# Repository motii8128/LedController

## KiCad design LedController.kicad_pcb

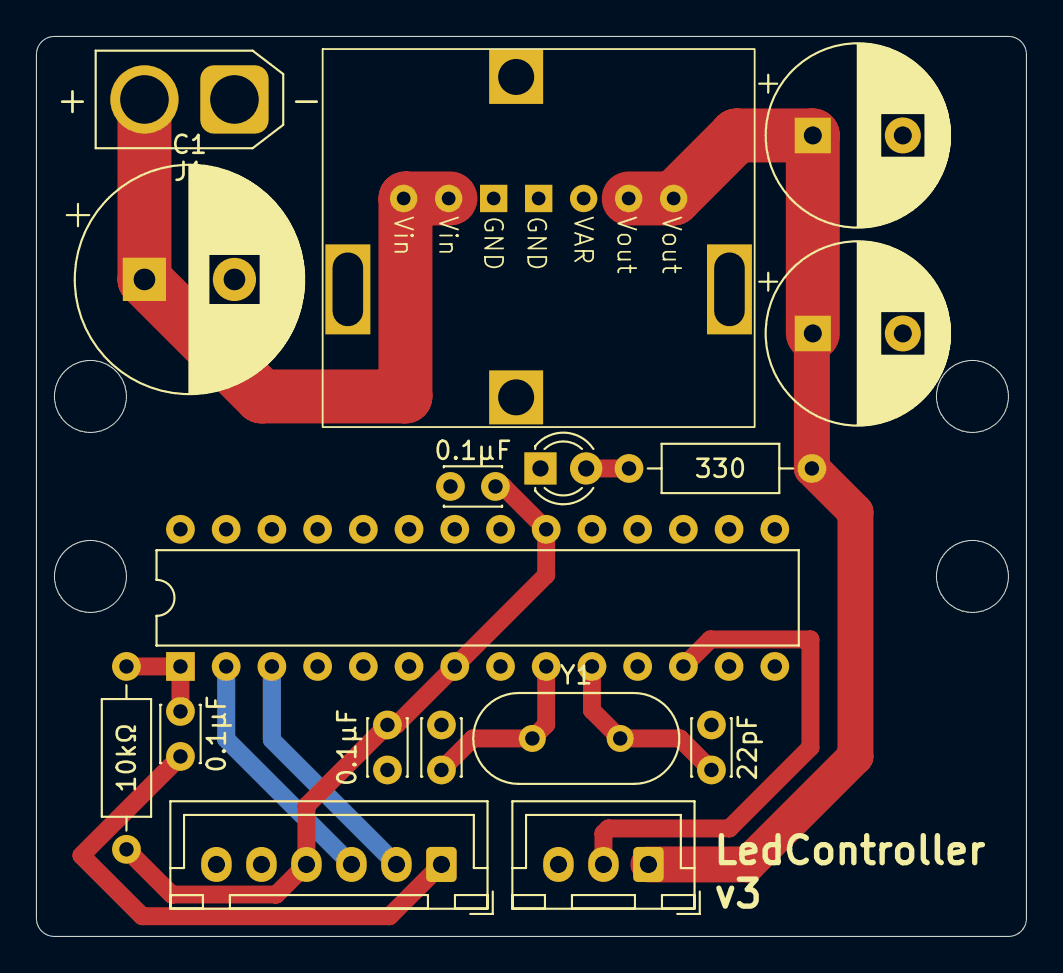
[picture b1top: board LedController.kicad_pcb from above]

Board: 2 copper layers, 55.0 x 50.0 mm, 17 parts (0 on the bottom side), 12 nets.

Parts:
0.1μF, 0.1μF#2, 0.1μF#3: 0.1uF; C_Disc_D3.0mm_W2.0mm_P2.50mm
10kΩ, 330: 10kΩ; R_Axial_DIN0207_L6.3mm_D2.5mm_P10.16mm_Horizontal
22pF: 22pF; C_Disc_D3.0mm_W2.0mm_P2.50mm
1000μF10V: 1000uF10V; CP_Radial_D10.0mm_P5.00mm
C1: 1000uF50V; CP_Radial_D12.5mm_P5.00mm
C2: 1000uF10V; CP_Radial_D10.0mm_P5.00mm
C4: 22pF; C_Disc_D3.0mm_W2.0mm_P2.50mm
D1: LED; LED_D3.0mm
J1: Batt; AMASS_XT30U-M_1x02_P5.0mm_Vertical
J3: Output; JST_XH_B3B-XH-A_1x03_P2.50mm_Vertical
RST: USB; JST_XH_B6B-XH-A_1x06_P2.50mm_Vertical
U1: MPD7K020S
U2: ATmega328P-P; DIP-28_W7.62mm
Y1: 16MHz; Crystal_HC49-4H_Vertical

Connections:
+5V: 330.2, 1000μF10V.1, C2.1, J3.1, U1.6 (Vout), U1.7 (Vout)
GND: 0.1μF.2, 0.1μF#3.1, 22pF.2, 1000μF10V.2, C1.2, C2.2, C4.2, D1.1 (K), J1.1, J3.3, RST.6, U1.3 (GND), U1.4 (GND), U2.8 (GND), U2.22 (GND)
unnamed: 330.1, D1.2 (A)
unnamed: C1.1, J1.2, U1.1 (Vin), U1.2 (Vin)
unnamed: 0.1μF#2.1, RST.1
unnamed: J3.2, U2.12 (PD6)
unnamed: C4.1, U2.9 (XTAL1/PB6), Y1.1
unnamed: 22pF.1, U2.10 (XTAL2/PB7), Y1.2
unnamed: 0.1μF#2.2, 10kΩ.2, U2.1 (~RESET/PC6)
RXD: RST.2, U2.3 (PD1)
TXD: RST.3, U2.2 (PD0)
VCC: 0.1μF.1, 0.1μF#3.2, 10kΩ.1, RST.4, U2.7 (VCC), U2.20 (AVCC)

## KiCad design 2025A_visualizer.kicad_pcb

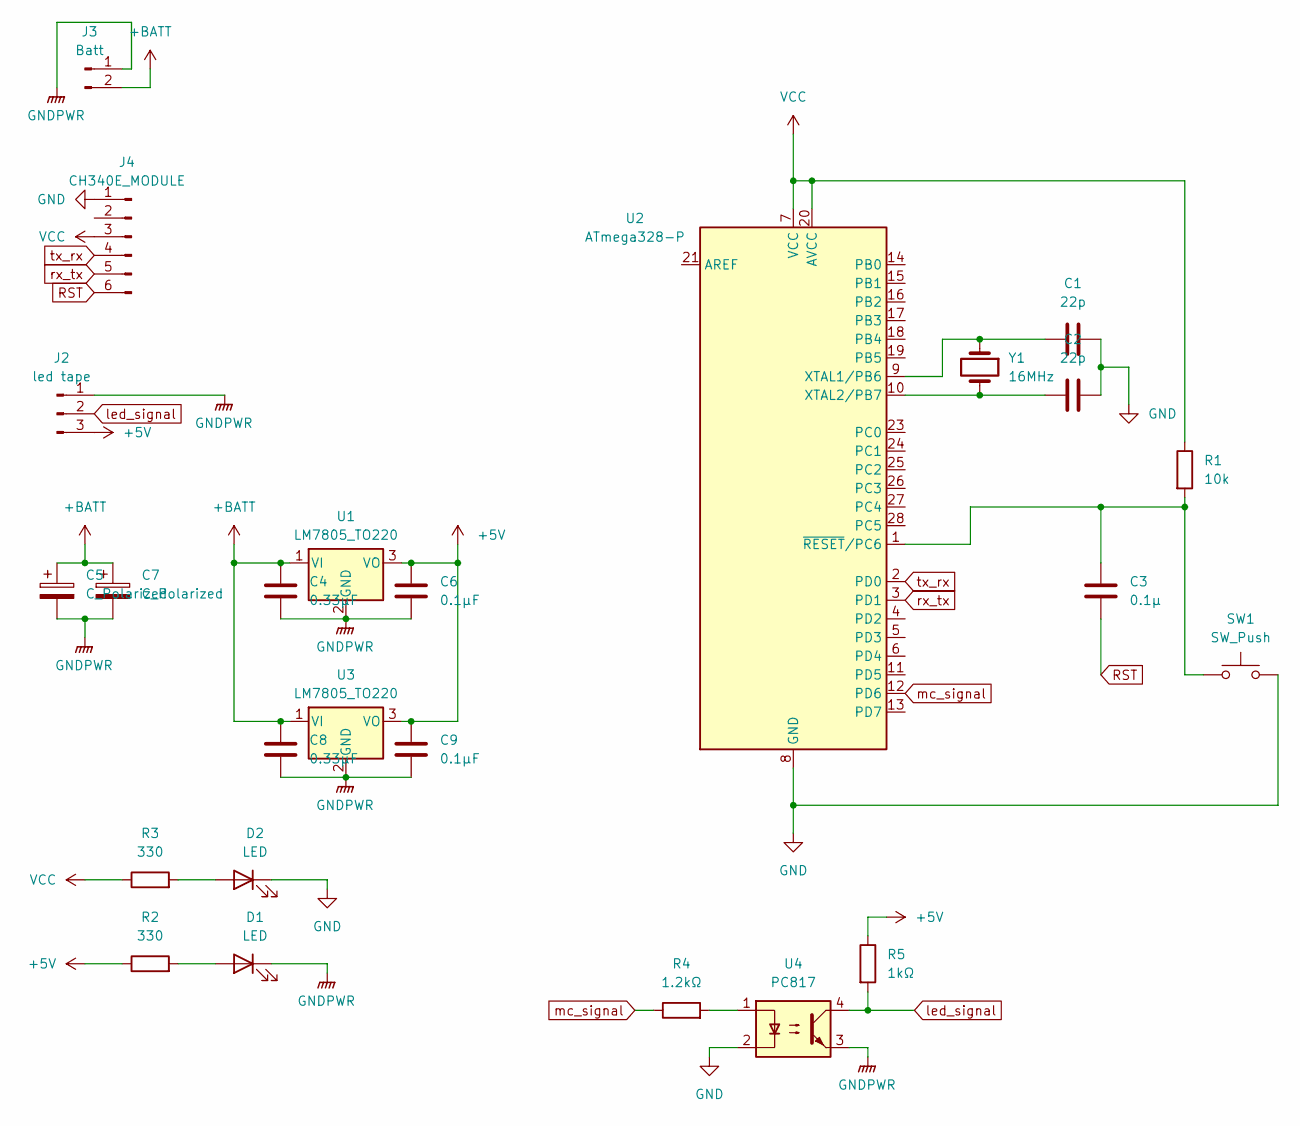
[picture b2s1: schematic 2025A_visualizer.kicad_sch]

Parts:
C1, C2: 22p; C_Disc_D3.0mm_W2.0mm_P2.50mm
C3: 0.1μ; C_Disc_D3.0mm_W2.0mm_P2.50mm
C4, C8: 0.33μF; C_Disc_D3.0mm_W2.0mm_P2.50mm
C5, C7: C_Polarized; C_Radial_D10.0mm_H16.0mm_P5.00mm
C6, C9: 0.1μF; C_Disc_D3.0mm_W2.0mm_P2.50mm
D1, D2: LED; LED_D3.0mm
J2: led tape; JST_XH_S3B-XH-A-1_1x03_P2.50mm_Horizontal
J3: Batt; AMASS_XT30PW-M_1x02_P2.50mm_Horizontal
J4: CH340E_MODULE; PinSocket_1x06_P2.54mm_Vertical
R1: 10k; R_Axial_DIN0207_L6.3mm_D2.5mm_P10.16mm_Horizontal
R2, R3: 330; R_Axial_DIN0207_L6.3mm_D2.5mm_P10.16mm_Horizontal
R4: 1.2kΩ; R_Axial_DIN0207_L6.3mm_D2.5mm_P10.16mm_Horizontal
R5: 1kΩ; R_Axial_DIN0207_L6.3mm_D2.5mm_P10.16mm_Horizontal
SW1: SW_Push; SW_PUSH_6mm
U1, U3: LM7805_TO220; TO-220-3_Horizontal_TabUp
U2: ATmega328-P; DIP-28_W7.62mm
U4: PC817; DIP-4_W7.62mm
Y1: 16MHz; Crystal_HC49-4H_Vertical

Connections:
+5V: C6.1, C9.1, J2.3, R2.1, R5.1, U1.3 (VO), U3.3 (VO)
+BATT: C4.1, C5.1, C7.1, C8.1, J3.2, U1.1 (VI), U3.1 (VI)
GND: C1.2, C2.2, D2.1 (K), J4.1, SW1.2, U2.8 (GND), U2.22 (GND), U4.2
GNDPWR: C4.2, C5.2, C6.2, C7.2, C8.2, C9.2, D1.1 (K), J2.1, J3.1, U1.2 (GND), U3.2 (GND), U4.3
unnamed: D1.2 (A), R2.2
unnamed: D2.2 (A), R3.2
unnamed: R4.2, U4.1
unnamed: C1.1, U2.9 (XTAL1/PB6), Y1.1
unnamed: C2.1, U2.10 (XTAL2/PB7), Y1.2
unnamed: C3.1, R1.2, SW1.1, U2.1 (~RESET/PC6)
RST: C3.2, J4.6
VCC: J4.3, R1.1, R3.1, U2.7 (VCC), U2.20 (AVCC)
led_signal: J2.2, R5.2, U4.4
mc_signal: R4.1, U2.12 (PD6)
rx_tx: J4.5, U2.3 (PD1)
tx_rx: J4.4, U2.2 (PD0)

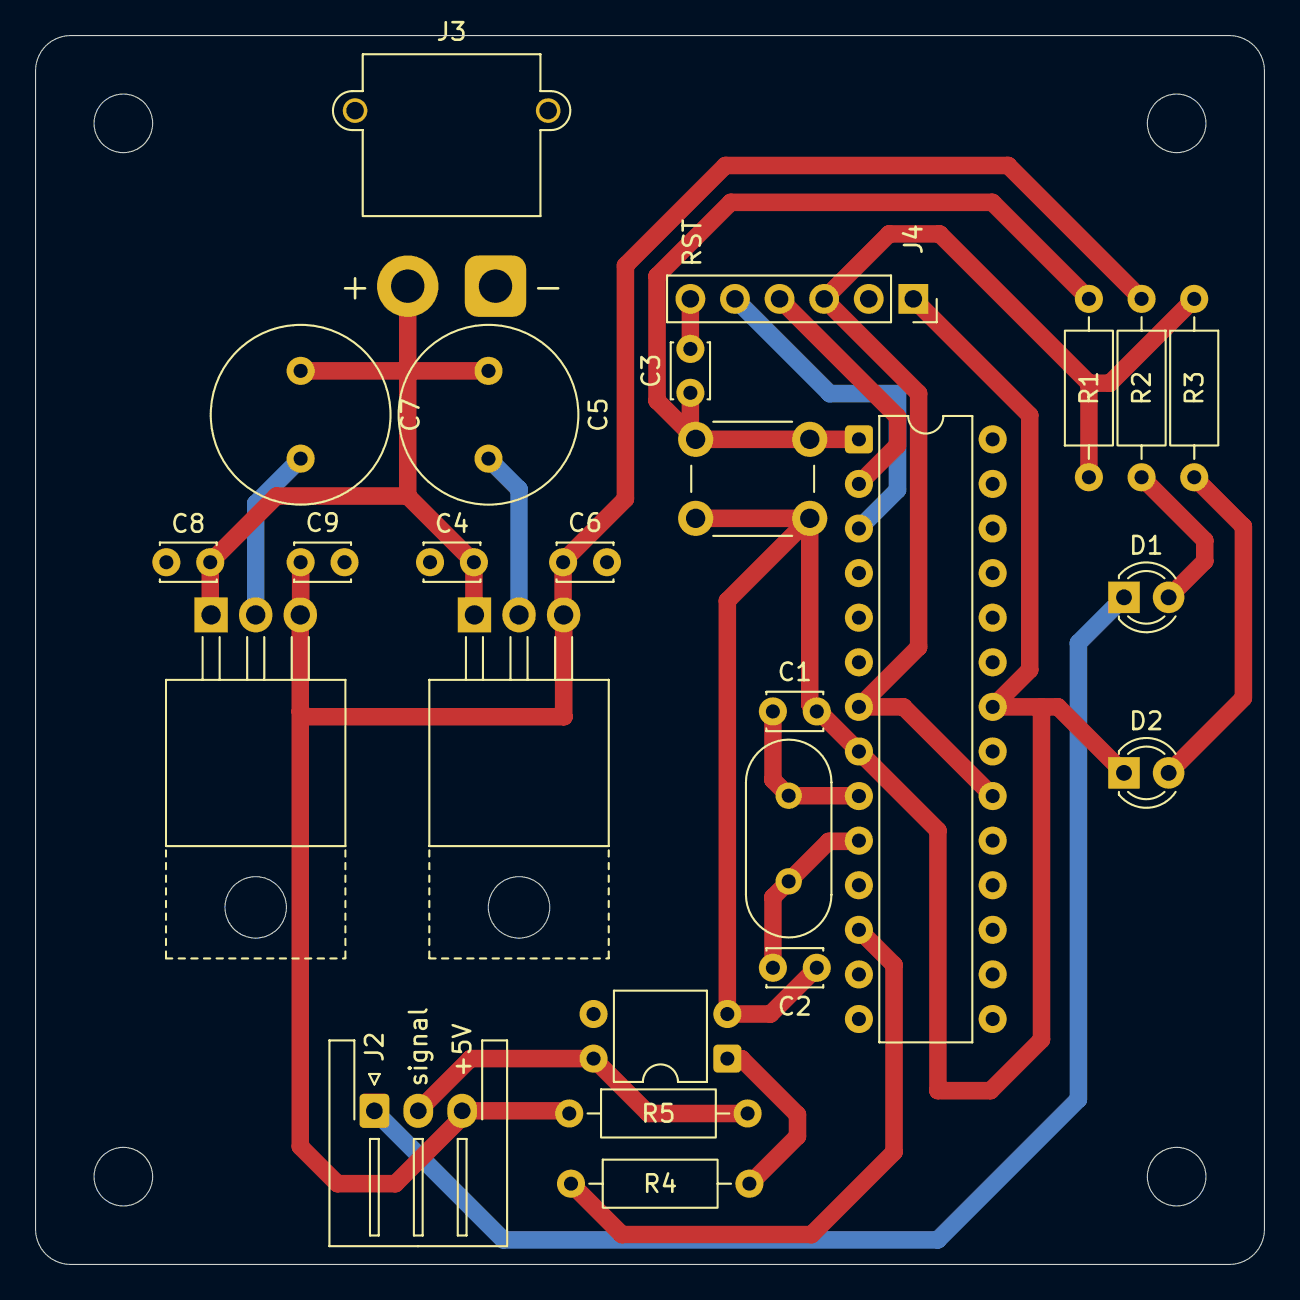
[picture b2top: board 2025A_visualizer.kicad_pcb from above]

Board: 2 copper layers, 70.0 x 70.0 mm, 25 parts (0 on the bottom side), 16 nets.

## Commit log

2025-10-24 add v3 data files
